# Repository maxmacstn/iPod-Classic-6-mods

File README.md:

# iPod Classic Mods
My attempt at modernizing the iPod Classic (6th generation) includes the following:

- [USB-C Mod](https://github.com/maxmacstn/iPod-Classic-6-mods/tree/main/Mods/USB-C) – Converts the 30-pin dock connector to a USB-C interface.

- [Bluetooth Audio Mod](https://github.com/maxmacstn/iPod-Classic-6-mods/tree/main/Mods/ESP32-Bluetooth-Audio) – Enables audio transmission to headphones or speakers via Bluetooth, with playback control.

- Taptic Engine – Replaces the clicking sound (from the buzzer) with haptic feedback. There are a bunch of videos out there on how to do this mod, so I haven’t included it in this repo. I used a Taptic Engine from an iPhone 11 Plus. It's small and provides a nice, firm vibration.

Click the link above to see the details.

### Video : [**Youtube (TH)**](https://youtu.be/0jGxkwJ26Vk)

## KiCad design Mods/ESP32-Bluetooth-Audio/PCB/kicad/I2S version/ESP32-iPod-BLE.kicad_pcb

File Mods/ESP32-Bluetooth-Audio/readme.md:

# Bluetooth Audio Mod
The iPod Classic does not have any built-in radio. The only way to listen to music is by physically connecting to the 3.5mm audio jack or the dock connector.

For the Bluetooth mod, people usually use off-the-shelf Bluetooth transmitter modules connected to the headphone output. This method works, but the audio quality isn't the best, and you can't control playback via Bluetooth headphones or speakers.

Instead of using an off-the-shelf Bluetooth transmitter module, I made my own Bluetooth board for this purpose. The main controller is an ESP32.

## Version 1 - Music via I2S

When the iPod produces sound, it sends a digital audio signal from the CPU to the DAC via the I2S protocol. The digital signal is then converted into an analog signal, which is the sound we hear through headphones. To preserve the original sound quality, tapping into the I2S signal is the way to go.

I didn’t coin the idea of hijacking the I2S signal from the iPod. I found [this really cool project](https://github.com/lemonjesus/iPodBluetooth) by @lemonjesus, where he successfully did this with his iPod Nano 3rd gen. I wanted to apply this concept to my iPod Classic 6th gen as well.

From my research, the iPod Classic 6th gen uses a DAC from Cirrus Logic — allegedly the CS42L55. I checked the pinout from the datasheet, and it matches.

Long story short, this version of the iPod uses a not-so-standard I2S protocol. While the signal is technically I2S, the BCLK line runs at a very high speed (12 MHz) and also acts as MCLK. The word length is also not 16-bit. After months of trying, I wasn’t able to get it working properly with the ESP32. I gave up using I2S as the audio source from the iPod Classic.

However, I bought a Nano 3rd gen, and my Bluetooth board works as expected with it.

## Version 2 - Music via Line Out

### Design 
Instead of using I2S, I used the line-out signal from the dock connector. The analog audio signal from the line-out is converted back to digital I2S using an ADC—specifically the PCM1860.

For playback control, external accessories can control the iPod via the dock connector using a serial protocol. There are a bunch of [examples online](https://github.com/finsprings/arduinaap). I’ve already prepared breakout pads for both the line-out and serial connections from the USB-C mod.

### Sound Quality
Definitely not as good as the original source since the audio goes through double conversion. I would say the sound quality is neither great nor terrible — it's acceptable. When listening through high-quality headphones or speakers, I can hear very subtle digital noise from interference. I even tried connecting the line-out directly from the DAC IC, but the noise was still there. So, I applied a simple filter: if the signal amplitude is very low, I set it to zero. I think this is good enough. The noise is mostly inaudible when music is playing.

### Power
I soldered the VBATT line after it passes through the power management IC. As a result, it's powered off along with the iPod. However, it doesn’t sleep when the iPod sleeps. So I implemented a check on the audio signal — if it's silent for five minutes, the Bluetooth board goes into deep sleep. There is still a small current draw, which drains the iPod’s battery in a few days. Initially, I used the 1.8V bus to enable the ESP32's power regulator, but that method stopped working for some reason, and I’ve been too lazy to fix it.

The original battery gives around 2 hours of Bluetooth music playback. This is just a proof of concept, and the battery life isn’t great.

### Bluetooth usage
I intended to not modify any sofware on the iPod, so how I could pair bluetooth device from the iPod, here's the step.
1. Restart the iPod by holding `SELECT` + `MENU`. This cuts off the power to the iPod, as well as the bluetooth board.
2. Once connected to the power, the bluetooth board starts discovering bluetooth audio device, then connected to the nearest (strongest signal) one.
3. Enjoy the music via bluetooth.
4. If there's no audio for 5 minutes, the Bluetooth board (ESP32) goes into deep sleep—until power is cut and reconnected.

### Signal
The iPod Classic has a metal front and back plate, which basically makes it a Faraday cage — signal can’t pass through easily. I removed the metal support underneath the display, which allows the signal to pass through a bit, but the range is still very limited (<1m). This could be easily fixed by 3D printing a plastic back cover—but that’s for later.

***TBC***

### Images

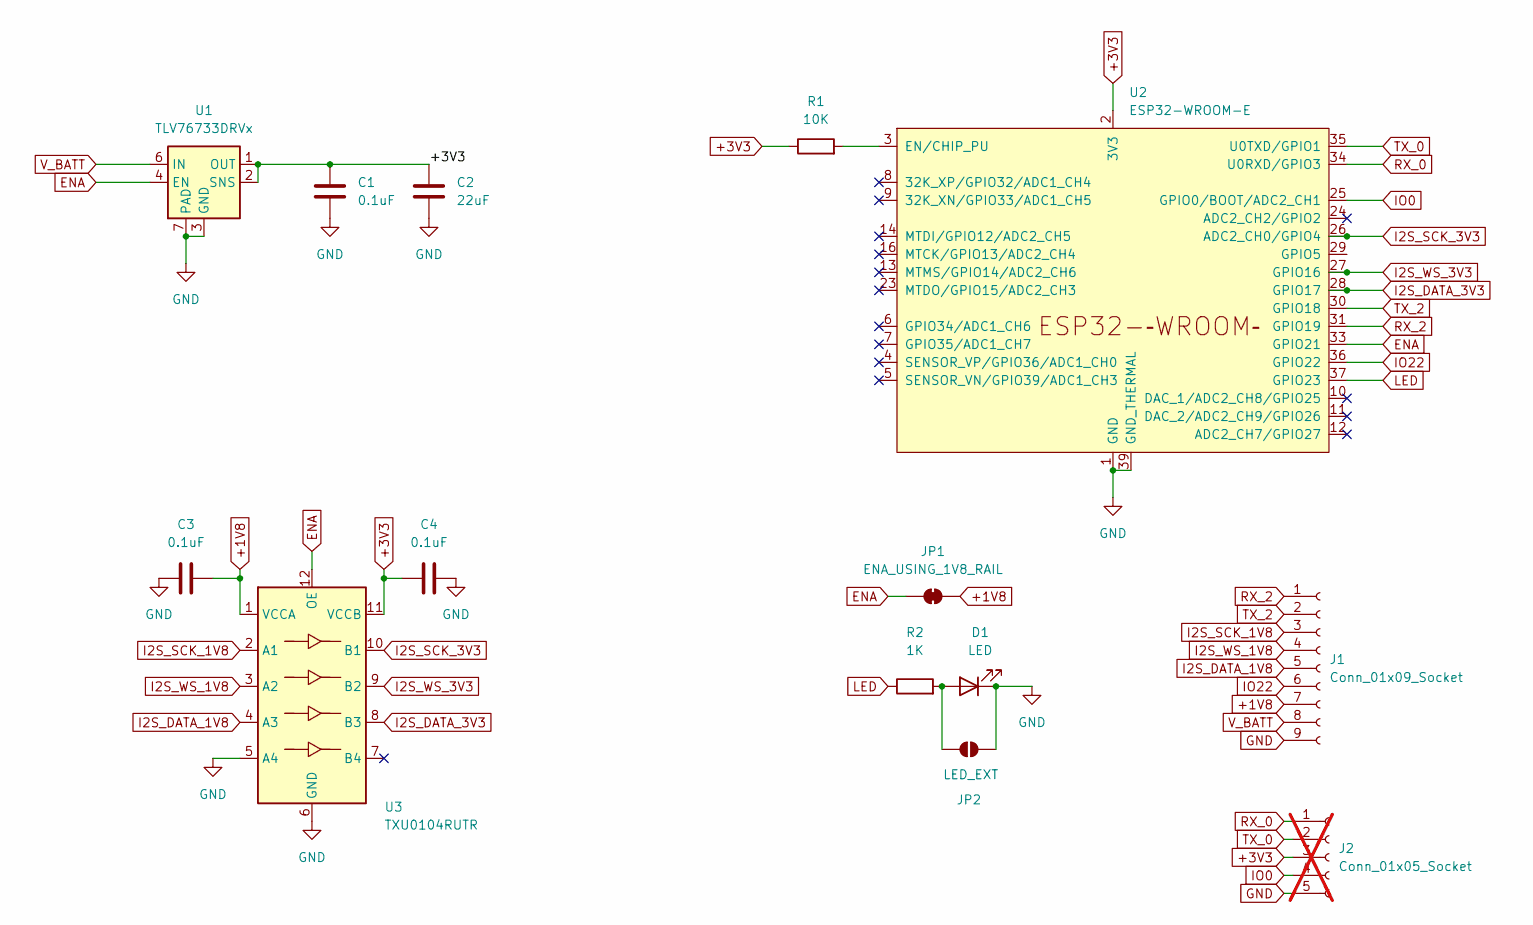
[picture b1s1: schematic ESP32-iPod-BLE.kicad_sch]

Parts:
C1, C3, C4: 0.1uF; C_0402_1005Metric; LCSC C110251
C2: 22uF; C_0805_2012Metric; LCSC C5674
D1: LED; LED_0603_1608Metric; LCSC C434421
J1: Conn_01x09_Socket; JST_ZH_S9B-ZR-SM4A-TF_1x09-1MP_P1.50mm_Horizontal
J2: Conn_01x05_Socket; PinHeader_1x05_P2.54mm_Vertical; not fitted
JP1: ENA_USING_1V8_RAIL; SolderJumper-2_P1.3mm_Bridged_Pad1.0x1.5mm
JP2: LED_EXT; SolderJumper-2_P1.3mm_Open_Pad1.0x1.5mm
R1: 10K; R_0402_1005Metric; LCSC C60490
R2: 1K; R_0402_1005Metric; LCSC C106235
U1: TLV76733DRVx; WSON-6-1EP_2x2mm_P0.65mm_EP1x1.6mm_ThermalVias; LCSC C2848334
U2: ESP32-WROOM-E; ESP32-WROOM-32E; LCSC C701341
U3: TXU0104RUTR; Texas_R-PUQFN-N12; LCSC C5187176

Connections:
+1V8: C3.2, J1.7, JP1.2 (B), U3.1 (VCCA)
+3V3: C1.1, C2.1, C4.1, J2.3, R1.1, U1.1 (OUT), U1.2 (SNS), U2.2 (3V3), U3.11 (VCCB)
ENA: JP1.1 (A), U1.4 (EN), U2.33 (GPIO21), U3.12 (OE)
GND: C1.2, C2.2, C3.1, C4.2, D1.1 (K), J1.9, J2.5, JP2.1 (A), U1.3 (GND), U1.5 (GND), U1.7 (PAD), U2.1 (GND), U2.15 (GND), U2.38 (GND), U2.39 (GND_THERMAL), U3.5 (A4), U3.6 (GND)
I2S_DATA_1V8: J1.5, U3.4 (A3)
I2S_DATA_3V3: U2.28 (GPIO17), U3.8 (B3)
I2S_SCK_1V8: J1.3, U3.2 (A1)
I2S_SCK_3V3: U2.26 (ADC2_CH0/GPIO4), U3.10 (B1)
I2S_WS_1V8: J1.4, U3.3 (A2)
I2S_WS_3V3: U2.27 (GPIO16), U3.9 (B2)
IO0: J2.4, U2.25 (GPIO0/BOOT/ADC2_CH1)
IO22: J1.6, U2.36 (GPIO22)
LED: R2.1, U2.37 (GPIO23)
unnamed: D1.2 (A), JP2.2 (B), R2.2
unnamed: R1.2, U2.3 (EN/CHIP_PU)
RX_0: J2.1, U2.34 (U0RXD/GPIO3)
RX_2: J1.1, U2.31 (GPIO19)
TX_0: J2.2, U2.35 (U0TXD/GPIO1)
TX_2: J1.2, U2.30 (GPIO18)
V_BATT: J1.8, U1.6 (IN)

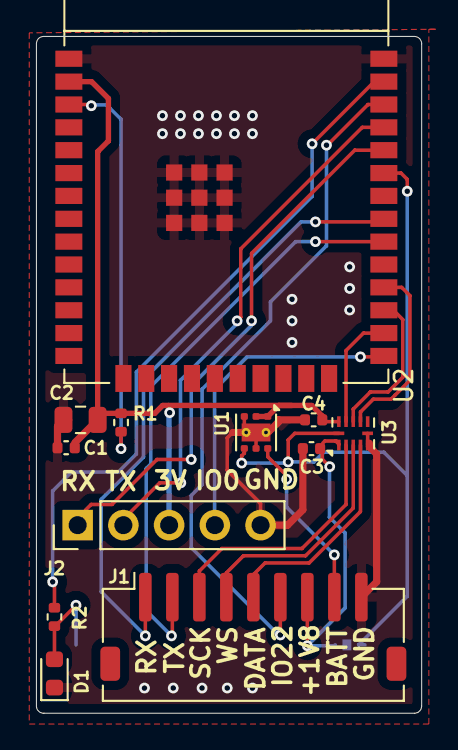
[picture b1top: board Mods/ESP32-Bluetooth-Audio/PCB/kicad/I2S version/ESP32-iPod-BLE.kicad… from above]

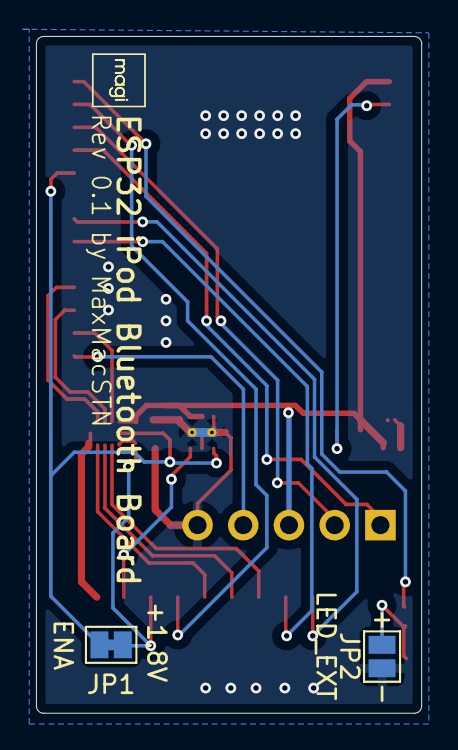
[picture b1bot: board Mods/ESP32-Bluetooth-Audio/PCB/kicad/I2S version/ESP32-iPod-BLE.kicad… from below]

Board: 2 copper layers, 21.4 x 37.6 mm, 14 parts (2 on the bottom side), 20 nets.

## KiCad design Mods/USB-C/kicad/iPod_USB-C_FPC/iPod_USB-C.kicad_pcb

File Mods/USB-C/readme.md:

# USB-C Mod

## Why
As we know, the 30-pin dock connector is an outdated interface that's no longer commonly used. This mod replaces the dock connector with a USB-C port. Keep in mind that you'll lose support for other dock connector features and won't be able to use 30-pin accessories anymore. For me, the convenience of USB-C makes it a no-brainer.

## Design

The dock connector is ancient. How it works is each pin has a specific purpose, e.g. USB, FireWire, line out, serial, etc. Therefore, it has many pins. What I did was tap into the USB D+, D−, VCC, and GND from the dock connector and connect them to a USB-C port. Seems simple, doesn't it?

However, the depth of the USB-C port is longer than the 30-pin dock connector. The PCB part that holds the USB-C port sits over the dock connector solder pads. What I did was create two parts: a solid PCB and a flexible PCB. The solid PCB holds the USB-C connector as well as attaches the PCB itself to the iPod's circuit board. The flexible PCB, aka FPC, connects the corresponding pins from the dock connector solder pads to the solid PCB. The FPC bends 180° to connect to the PCB using a Molex mezzanine connector. Don't forget to put some tape on the bottom of the PCB to avoid shorting to the dock connector pads.

The PCB includes three 0603 resistors—two for enabling charging with USB-C PD adapters, and one (optional) for iPod accessory identification. Additionally, there are four soldering pads connected to the dock connector: Line_L, Line_R (for audio line out), and TX, RX (for serial communication). These are used for other mods, like the Bluetooth audio mod, which I used it.

Finally, the port bezel, attached to the iPod’s back cover, had to be replaced. I designed a new bezel for the USB-C port and 3D printed it using an FDM printer. After some sanding and painting, it now has a nice glossy finish.

## How hard if I want one?
I am not going to sell it. I have provided all the files, including the KiCad project, Gerber files, bill of materials, as well as the 3D file in this repository. If you dare to solder these tiny parts, you’ll need to fabricate them yourself through a PCB manufacturer of your choice.

I'm not a microsoldering expert, but I would say I have intermediate soldering skills. It's still quite challenging. For me, the hardest part was soldering the mezzanine connectors.

## Conclusion
USB-C works perfectly fine. It connects to the computer as well as the car's infotainment system—no issues so far. The charging function and speed are the same as the original. The Apple original charger is still needed for the iPod to display the charging icon, or you can charge via a PC.

## Images

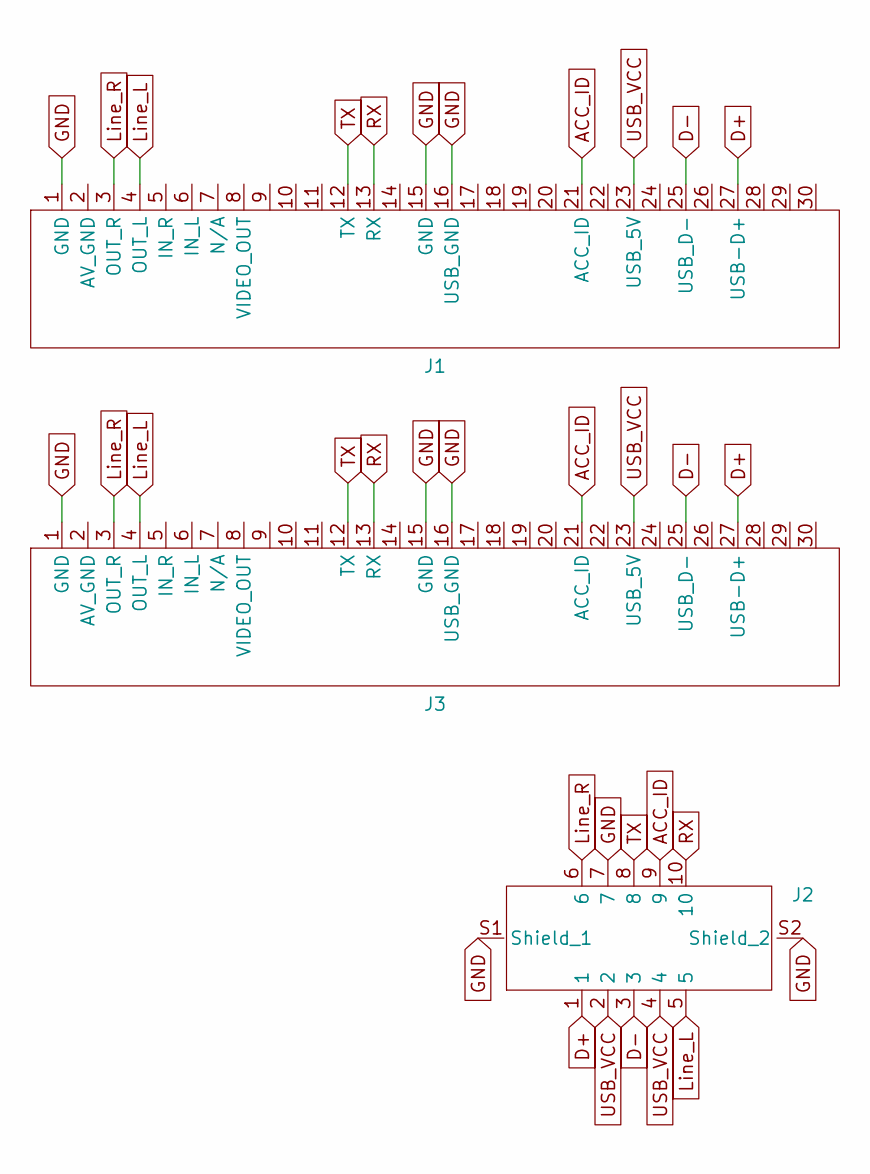
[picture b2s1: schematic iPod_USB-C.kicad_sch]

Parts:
J1, J3: SolderPad_iPod_Dock
J2: MOLEX_505070_1022

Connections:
ACC_ID: J1.21 (ACC_ID), J2.9, J3.21 (ACC_ID)
D+: J1.27 (USB-D+), J2.1, J3.27 (USB-D+)
D-: J1.25 (USB_D-), J2.3, J3.25 (USB_D-)
GND: J1.1 (GND), J1.15 (GND), J1.16 (USB_GND), J2.7, J2.S1 (Shield_1), J2.S2 (Shield_2), J3.1 (GND), J3.15 (GND), J3.16 (USB_GND)
Line_L: J1.4 (OUT_L), J2.5, J3.4 (OUT_L)
Line_R: J1.3 (OUT_R), J2.6, J3.3 (OUT_R)
RX: J1.13 (RX), J2.10, J3.13 (RX)
TX: J1.12 (TX), J2.8, J3.12 (TX)
USB_VCC: J1.23 (USB_5V), J2.2, J2.4, J3.23 (USB_5V)

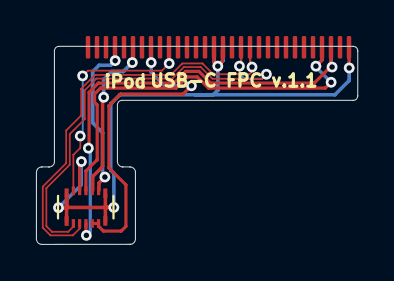
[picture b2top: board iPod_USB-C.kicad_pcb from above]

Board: 2 copper layers, 17.9 x 11.0 mm, 3 parts (1 on the bottom side), 9 nets.

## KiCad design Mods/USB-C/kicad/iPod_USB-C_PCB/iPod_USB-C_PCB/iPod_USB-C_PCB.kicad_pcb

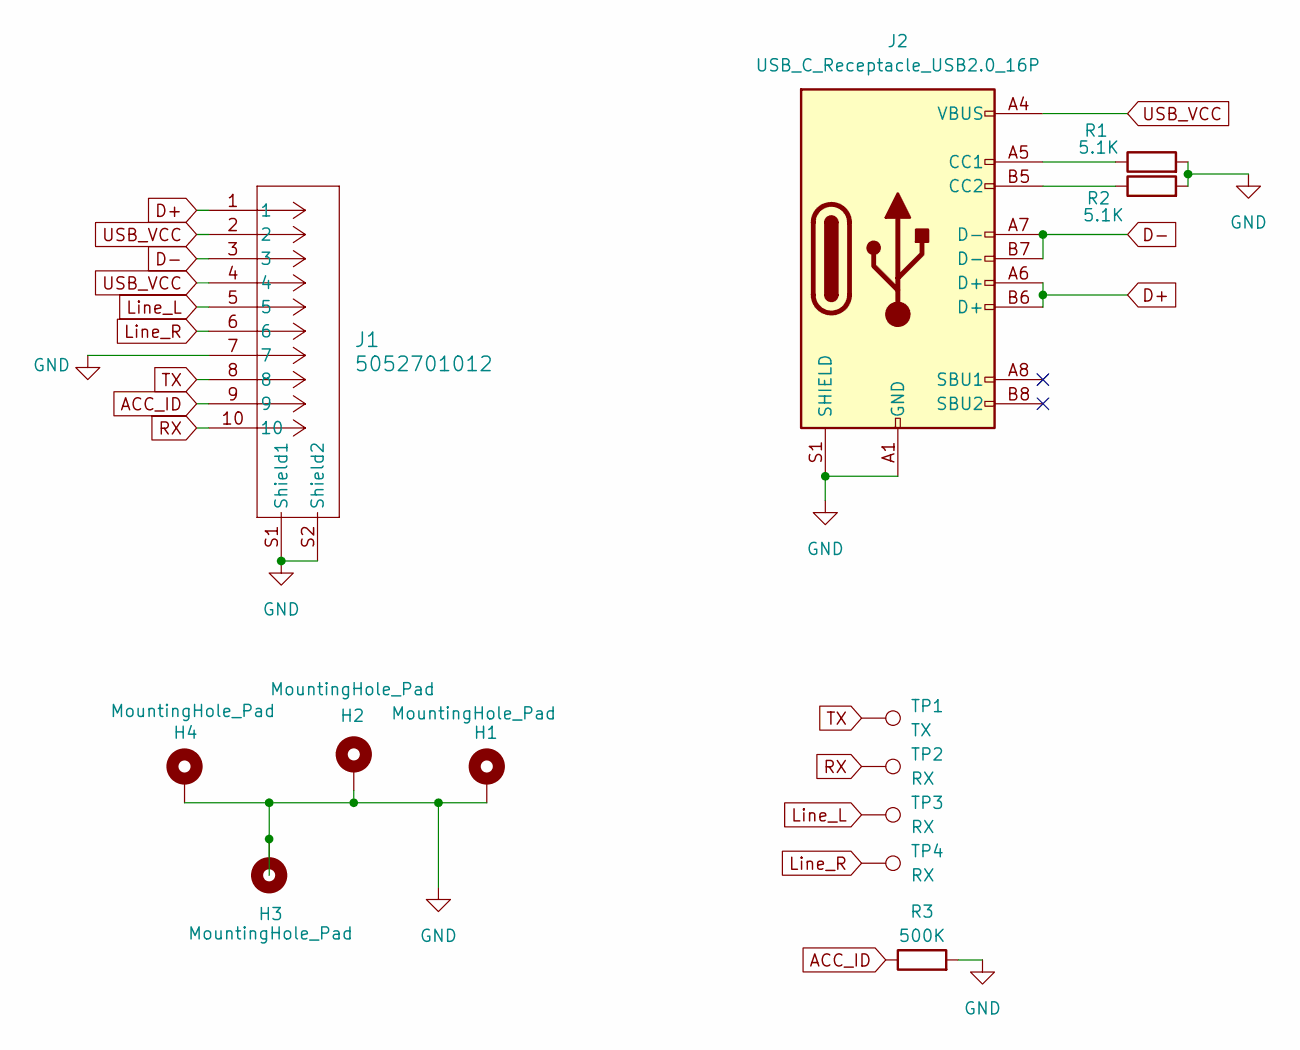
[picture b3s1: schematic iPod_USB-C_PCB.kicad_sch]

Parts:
H1, H2, H3, H4: MountingHole_Pad; iPod_USB-C_PCB_mount
J1: 5052701012; MOLEX_505270_1012
J2: USB_C_Receptacle_USB2.0_16P; USB_C_Receptacle_GCT_USB4105-xx-A_16P_TopMnt_Horizontal
R1, R2: 5.1K; R_0603_1608Metric
R3: 500K; R_0603_1608Metric
TP1: TX; TestPoint_Pad_1.0x1.0mm
TP2, TP3, TP4: RX; TestPoint_Pad_1.0x1.0mm

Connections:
ACC_ID: J1.9, R3.1
D+: J1.1, J2.A6 (D+), J2.B6 (D+)
D-: J1.3, J2.A7 (D-), J2.B7 (D-)
GND: H1.1, H2.1, H3.1, H4.1, J1.7, J1.S1 (Shield1), J1.S2 (Shield2), J2.A1 (GND), J2.A12 (GND), J2.B1 (GND), J2.B12 (GND), J2.S1 (SHIELD), R1.2, R2.2, R3.2
Line_L: J1.5, TP3.1
Line_R: J1.6, TP4.1
unnamed: J2.A5 (CC1), R1.1
unnamed: J2.B5 (CC2), R2.1
RX: J1.10, TP2.1
TX: J1.8, TP1.1
USB_VCC: J1.2, J1.4, J2.A4 (VBUS), J2.A9 (VBUS), J2.B4 (VBUS), J2.B9 (VBUS)

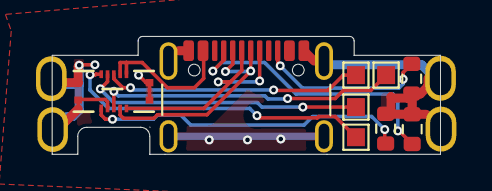
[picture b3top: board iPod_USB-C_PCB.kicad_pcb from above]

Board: 2 copper layers, 21.6 x 6.5 mm, 13 parts (0 on the bottom side), 11 nets.

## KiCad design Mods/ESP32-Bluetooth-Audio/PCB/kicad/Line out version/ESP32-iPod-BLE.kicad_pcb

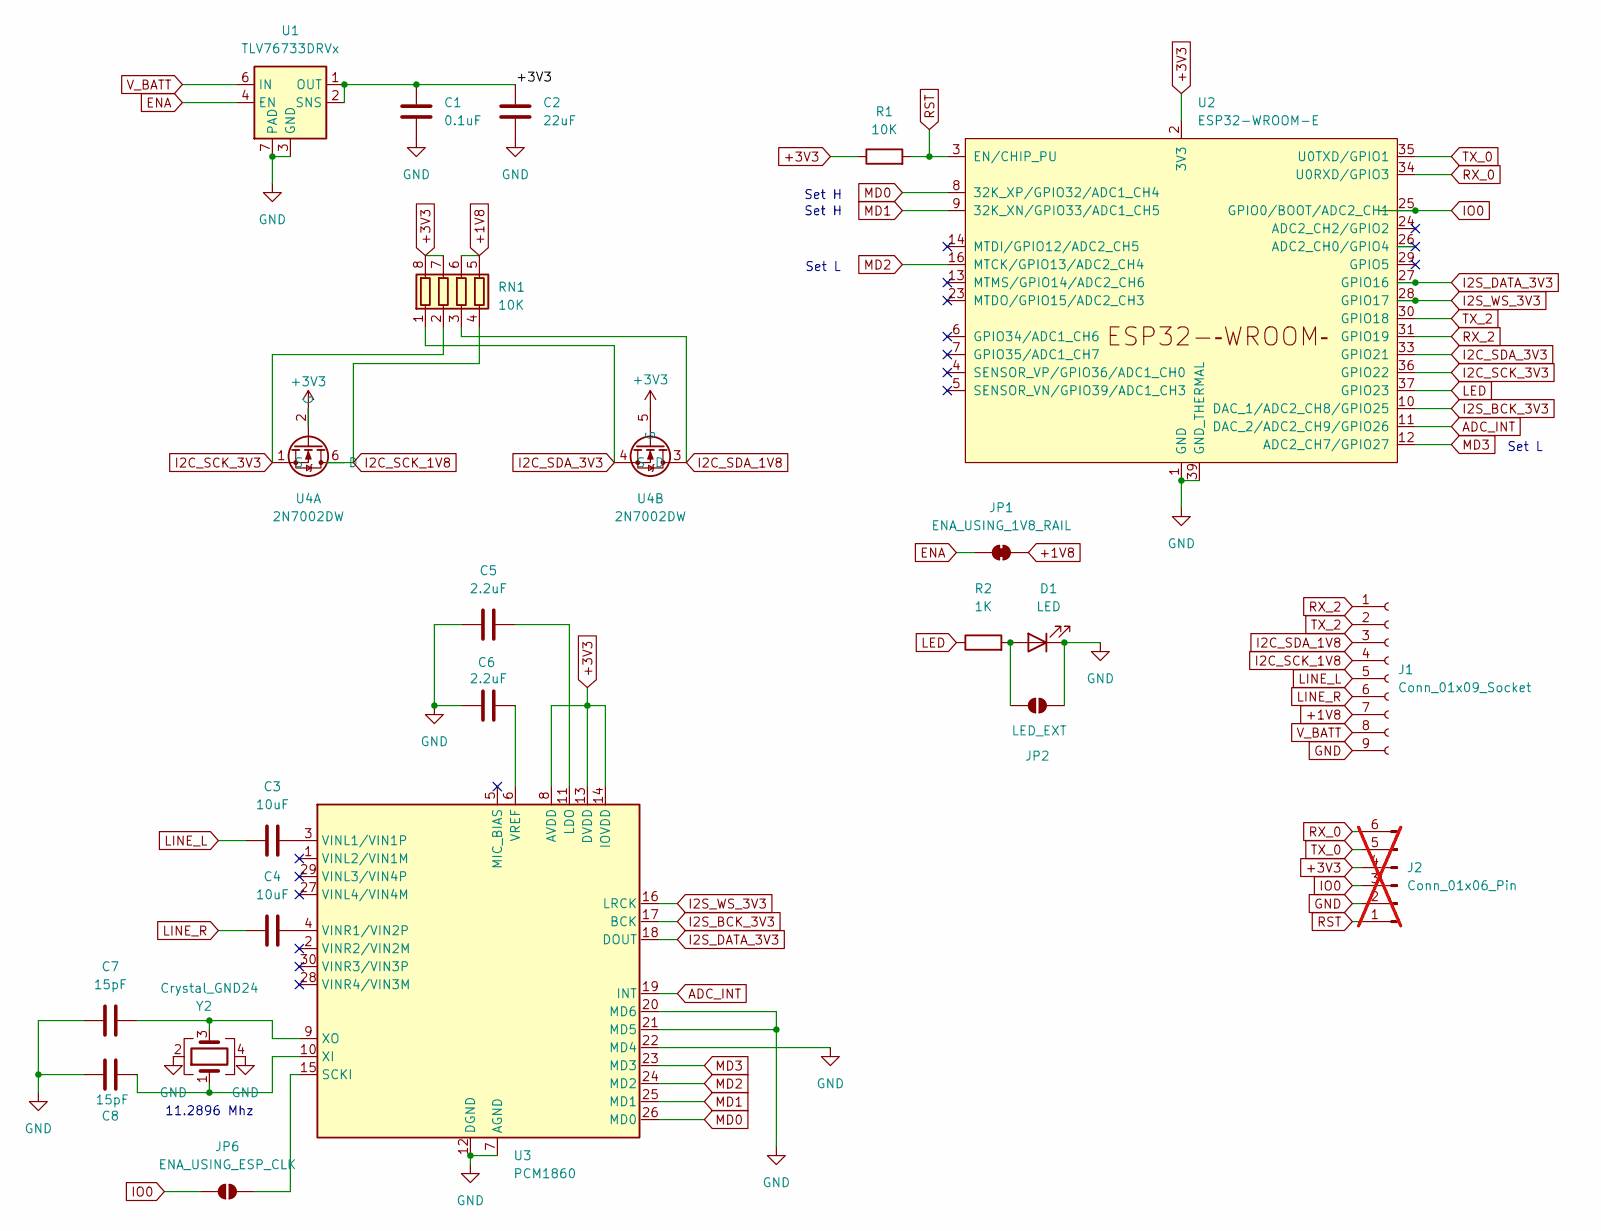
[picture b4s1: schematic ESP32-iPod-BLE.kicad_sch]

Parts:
C1: 0.1uF; C_0402_1005Metric; LCSC C110251
C2: 22uF; C_0805_2012Metric; LCSC C5674
C3, C4: 10uF; C_0805_2012Metric; LCSC C1713
C5, C6: 2.2uF; C_0402_1005Metric; LCSC C12530
C7, C8: 15pF; C_0402_1005Metric; LCSC C106997
D1: LED; LED_0603_1608Metric; LCSC C434421
J1: Conn_01x09_Socket; JST_ZH_S9B-ZR-SM4A-TF_1x09-1MP_P1.50mm_Horizontal
J2: Conn_01x06_Pin; PinHeader_1x06_P2.54mm_Vertical; not fitted
JP1: ENA_USING_1V8_RAIL; SolderJumper-2_P1.3mm_Bridged_Pad1.0x1.5mm
JP2: LED_EXT; SolderJumper-2_P1.3mm_Open_Pad1.0x1.5mm
JP6: ENA_USING_ESP_CLK; SolderJumper-2_P1.3mm_Open_RoundedPad1.0x1.5mm
R1: 10K; R_0402_1005Metric; LCSC C60490
R2: 1K; R_0402_1005Metric; LCSC C106235
RN1: 10K; R_Array_Convex_4x0603; LCSC C29718
U1: TLV76733DRVx; WSON-6-1EP_2x2mm_P0.65mm_EP1x1.6mm_ThermalVias; LCSC C2848334
U2: ESP32-WROOM-E; ESP32-WROOM-32E; LCSC C701341
U3: PCM1860; TSSOP-30_4.4x7.8mm_P0.5mm; LCSC C1520799
U4: 2N7002DW; SOT-363_SC-70-6; LCSC C83571
Y2: Crystal_GND24; Crystal_SMD_3225-4Pin_3.2x2.5mm; LCSC C654945

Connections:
+1V8: J1.7, JP1.2 (B), RN1.5 (R4.2), RN1.6 (R3.2)
+3V3: C1.1, C2.1, J2.4, R1.1, RN1.7 (R2.2), RN1.8 (R1.2), U1.1 (OUT), U1.2 (SNS), U2.2 (3V3), U3.8 (AVDD), U3.13 (DVDD), U3.14 (IOVDD), U4.2 (G), U4.5 (G)
ADC_INT: U2.11 (DAC_2/ADC2_CH9/GPIO26), U3.19 (INT)
ENA: JP1.1 (A), U1.4 (EN)
GND: C1.2, C2.2, C5.2, C6.1, C7.1, C8.1, D1.1 (K), J1.9, J2.2, JP2.1 (A), U1.3 (GND), U1.5 (GND), U1.7 (PAD), U2.1 (GND), U2.15 (GND), U2.38 (GND), U2.39 (GND_THERMAL), U3.7 (AGND), U3.12 (DGND), U3.20 (MD6), U3.21 (MD5), U3.22 (MD4), Y2.2, Y2.4
I2C_SCK_1V8: J1.4, RN1.4 (R4.1), U4.6 (D)
I2C_SCK_3V3: RN1.2 (R2.1), U2.36 (GPIO22), U4.1 (S)
I2C_SDA_1V8: J1.3, RN1.3 (R3.1), U4.3 (D)
I2C_SDA_3V3: RN1.1 (R1.1), U2.33 (GPIO21), U4.4 (S)
I2S_BCK_3V3: U2.10 (DAC_1/ADC2_CH8/GPIO25), U3.17 (BCK)
I2S_DATA_3V3: U2.27 (GPIO16), U3.18 (DOUT)
I2S_WS_3V3: U2.28 (GPIO17), U3.16 (LRCK)
IO0: J2.3, JP6.1 (A), U2.25 (GPIO0/BOOT/ADC2_CH1)
LED: R2.1, U2.37 (GPIO23)
LINE_L: C3.1, J1.5
LINE_R: C4.1, J1.6
MD0: U2.8 (32K_XP/GPIO32/ADC1_CH4), U3.26 (MD0)
MD1: U2.9 (32K_XN/GPIO33/ADC1_CH5), U3.25 (MD1)
MD2: U2.16 (MTCK/GPIO13/ADC2_CH4), U3.24 (MD2)
MD3: U2.12 (ADC2_CH7/GPIO27), U3.23 (MD3)
unnamed: D1.2 (A), JP2.2 (B), R2.2
unnamed: JP6.2 (B), U3.15 (SCKI)
unnamed: C5.1, U3.11 (LDO)
unnamed: C3.2, U3.3 (VINL1/VIN1P)
unnamed: C4.2, U3.4 (VINR1/VIN2P)
unnamed: C6.2, U3.6 (VREF)
unnamed: C8.2, U3.10 (XI), Y2.1
unnamed: C7.2, U3.9 (XO), Y2.3
RST: J2.1, R1.2, U2.3 (EN/CHIP_PU)
RX_0: J2.6, U2.34 (U0RXD/GPIO3)
RX_2: J1.1, U2.31 (GPIO19)
TX_0: J2.5, U2.35 (U0TXD/GPIO1)
TX_2: J1.2, U2.30 (GPIO18)
V_BATT: J1.8, U1.6 (IN)

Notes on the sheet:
Set L
Set H
11.2896 Mhz

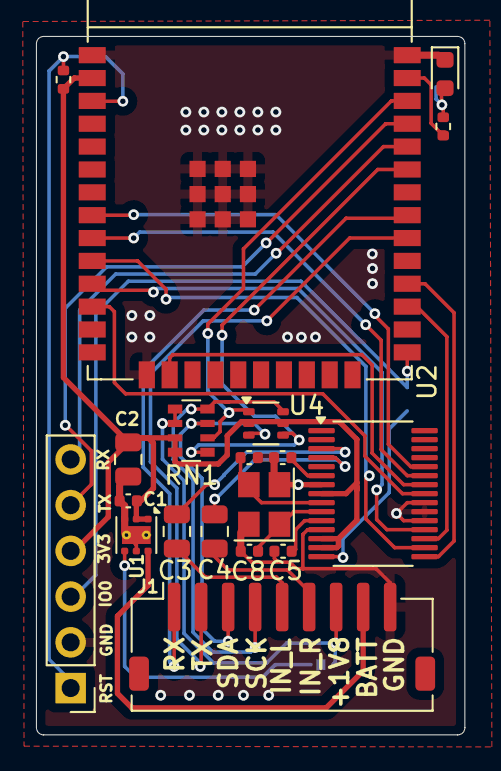
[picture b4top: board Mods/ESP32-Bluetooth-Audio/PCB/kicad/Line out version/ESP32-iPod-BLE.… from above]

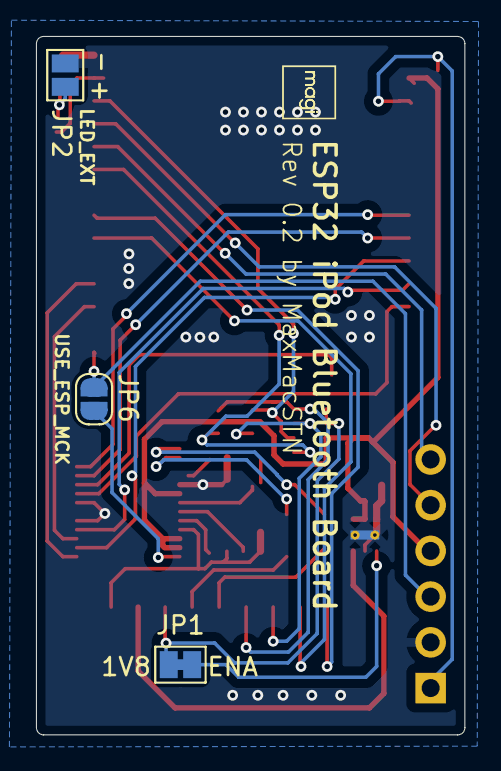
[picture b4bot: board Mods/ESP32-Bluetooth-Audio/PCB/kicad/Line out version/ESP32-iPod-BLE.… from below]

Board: 2 copper layers, 23.8 x 38.8 mm, 22 parts (3 on the bottom side), 34 nets.

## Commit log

2025-04-25 Init
